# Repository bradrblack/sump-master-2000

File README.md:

<br clear="both"/>

# Sump Master 2000

An ESP32-C3 sump pump monitor. It detects the pump running from its vibration,
measures the water level and the air temperature/humidity, sends everything to
InfluxDB (via Telegraf on the LAN) for a Grafana timeline, and pushes pump
events, alarms and a daily report to your phone with [ntfy.sh](https://ntfy.sh).

There's no cloud service in the data path: readings go to a database on your own
network. [PLAN.md](PLAN.md) has the design and the remaining open questions.

The sketch is `src/sm2k.ino`, with small drivers for the level sensor
(`src/jsn_sr04t.*`) and the AHT20 (`src/aht20.*`).

## What it does

- **Pump on/off:** a GY-346 (ADXL346) accelerometer clamped to the pump or the
  discharge pipe. Samples at 400 Hz, high-passes each axis (~13 Hz cutoff) to
  reject gravity, footsteps and house rumble, and computes RMS over 250 ms
  windows. `RUN_CONFIRM_MS` of continuous vibration above `ON_RMS_THRESHOLD`
  starts a run; `STOP_CONFIRM_MS` of quiet below `OFF_RMS_THRESHOLD` ends it
  (3 s each).
- **Water level:** a JSN-SR04T waterproof ultrasonic sensor under the pit lid.
  Every 5 s it takes the median of a burst of 5 pings (one per 250 ms window, so
  vibration sampling never waits), corrected for the speed of sound at the
  measured air temperature. Level is reported as water depth above the pit
  floor.
- **Temperature/humidity:** an AHT20 on the same I2C bus, read every 10 s and
  CRC-checked.
- **Data to InfluxDB:** pump start/stop as it happens, and every 10 minutes the
  level, temperature, humidity and pump activity. See [Data](#data).
- **Home Assistant (optional):** state over MQTT, found automatically through
  MQTT Discovery. See [Home Assistant](#home-assistant).
- **ntfy pushes:** see [Notifications](#notifications).
- **A web page on the board** (`http://sm2k.local/`): live readings, the recent
  log, and the calibration settings, changeable from a phone. See
  [Web page](#web-page).
- **OTA updates** pushed from your computer over Wi-Fi, with automatic rollback if the
  new firmware isn't healthy. See [Updating](#updating-firmware).

The onboard NeoPixel (GPIO 8, dimmed) shows the state: **green** = all clear,
**blue** = pump running, **flashing red** = high water with the pump not running,
**flashing purple** = high water with the pump running.

Serial output (115200) prints a status line once a second:
`rms=0.208 max=0.219 loud=0 state=idle level=12.3cm air=17.9C/71% wifi=up tgq=0`
(`rms` is the latest 250 ms window, `max` the loudest of that second, `loud`
how many of its windows reached the stop threshold, `tgq` the number of points
waiting to be sent to Telegraf).

## Hardware and wiring

| Part | Connection |
|------|------------|
| GY-346 (ADXL346) SDA / SCL | GPIO 5 / GPIO 6 |
| AHT20 SDA / SCL | GPIO 5 / GPIO 6 (same bus) |
| JSN-SR04T Trig | GPIO 3 |
| JSN-SR04T Echo | GPIO 4, **straight to the pin** (3.3 V board, no divider) |
| JSN-SR04T VCC / GND | SuperMini 3V3 / GND |
| Status LED | GPIO 8 (onboard NeoPixel) |
| Sensor supply capacitors | 470 µF across 3V3/GND at each I2C sensor |

GPIO 2, 8 and 9 are boot strapping pins on the C3, so nothing else uses them.

**I2C reliability:** the bus runs at **100 kHz**. At 400 kHz, with long jumper
wires and no capacitors, the sensors dropped out and the board sometimes crashed
inside the I2C driver on a cold power-up. Short direct wires plus a 470 µF
capacitor across 3V3/GND at each sensor fixed it (14 hours overnight and 5 of 5
cold power-ups clean). Keep the capacitors.

**GY-346 note:** the ADXL346 is register-compatible with the ADXL345 and uses
the same Adafruit library, but reports device ID `0xE6` rather than `0xE5`, which
the library's `begin()` rejects. The firmware accepts either chip and enables
measurement itself. Its CS and SDO pins can stay unconnected (the module has
pull resistors). The AHT20+BMP280 board's BMP280 (0x77) is unused.

**Level sensor power:** use a **newer JSN-SR04T / AJ-SR04M board that runs from
3.3 V**; its Echo is then 3.3 V and needs no divider. An older 5 V board needs
one: Echo → 1 kΩ → GPIO 4 and GPIO 4 → 2 kΩ → GND. Measure Echo before
connecting it. The firmware enables a weak pull-down on GPIO 4 so a
disconnected Echo can't fire the interrupt from radio noise.
[PLAN.md](PLAN.md#jsn-sr04t-wiring) has the details.

**PCB and case:** the carrier PCB and 3D-printed case are in [hw/](hw/).

**Mounting the level sensor:** the JSN-SR04T is blind closer than about 20-25 cm
and can then report a double echo (about twice the real distance), which would
read as "low" just as the pit overflows. Mount the transducer **at least 30 cm
above the highest level the water can reach** (the pit rim), on a bracket or
riser. Readings closer than 25 cm are treated as "at or above the limit", never
as a real distance.

## Setup

1. **Secrets:**
   ```
   cp src/secrets.h.example src/secrets.h
   cp secrets.ini.example secrets.ini
   ```
   `src/secrets.h` holds Wi-Fi, the Telegraf URL and the ntfy topic;
   `secrets.ini` holds the OTA password (letters and digits), used both to build
   the firmware and to authenticate uploads. Both are git-ignored.
2. **Pit settings** in `platformio.ini` (`[env:sump]`): `SENSOR_TO_FLOOR_CM`,
   `HIGH_WATER_CM`, `HIGH_WATER_HYST_CM`, `MIN_DROP_CM`. The values there are
   placeholders until the sensor is mounted; see [Calibration](#calibration).
3. **InfluxDB, Telegraf and Grafana:** the board needs somewhere to send its
   data. If you don't already run these, follow
   [Setting up InfluxDB, Telegraf and Grafana](#setting-up-influxdb-telegraf-and-grafana)
   below, then put the Telegraf URL in `TELEGRAF_URL`. (Skip it, and leave
   `TELEGRAF_URL` out of `secrets.h`, if you only want the ntfy pushes.)
4. **ntfy:** subscribe to your `NTFY_TOPIC` in the ntfy app.
5. **First flash over USB** (it installs the OTA partition table):
   `pio run -t upload`.

## Updating firmware

After the first USB flash, update over Wi-Fi from your computer:

```
pio run -e sump-ota -t upload
```

- The board is found as `sm2k.local` (change `upload_port` in `platformio.ini` to
  an IP address if mDNS doesn't resolve).
- Updates are only accepted while the pump is idle (an upload pauses sampling
  for ~15 s). If the pump is running the upload fails with no response; run it
  again once the pump stops.
- **Rollback:** a new image runs as a trial. After 3 minutes with Wi-Fi up and
  every sensor that was working before the update working again, it's marked
  good and ntfy says `sump updated A -> B`. If it isn't healthy within 10
  minutes, crashes, or reboots during the trial (including failing to join
  Wi-Fi), the bootloader switches back to the previous firmware and ntfy says
  `update rolled back` with the reason.
- Bump `FIRMWARE_VERSION` in `src/sm2k.ino` for each release.
- Recovery if all else fails: USB flash (`pio run -t upload`).

## Setting up InfluxDB, Telegraf and Grafana

Skip this if you already run them. The data path is:

```
Sump Master  --HTTP POST-->  Telegraf (port 8186)  -->  InfluxDB  <--  Grafana
 (ESP32-C3)                  receives the board's        stores the     draws the
                             data and forwards it        time series    dashboard
```

- **InfluxDB 2.x** is the time-series database that stores the readings.
- **Telegraf** is a small collector. Here it just accepts the board's POSTs and
  writes them to InfluxDB (so the board never needs InfluxDB's token).
- **Grafana** draws the dashboard and sends the "silent" alert.

You need a computer that's always on, on the same network as the board: a
Raspberry Pi, a NAS, a spare PC or a home server. The easiest way to run all
three is Docker.

### 1. Start the three services (Docker)

Install [Docker](https://docs.docker.com/get-docker/), make an empty folder, and
create `docker-compose.yml` in it (change the passwords and token):

```yaml
services:
  influxdb:
    image: influxdb:2
    restart: unless-stopped
    ports: ["8086:8086"]
    volumes: ["influx-data:/var/lib/influxdb2"]
    environment:
      DOCKER_INFLUXDB_INIT_MODE: setup
      DOCKER_INFLUXDB_INIT_USERNAME: admin
      DOCKER_INFLUXDB_INIT_PASSWORD: change-this-password
      DOCKER_INFLUXDB_INIT_ORG: home
      DOCKER_INFLUXDB_INIT_BUCKET: sump
      DOCKER_INFLUXDB_INIT_ADMIN_TOKEN: change-this-admin-token

  telegraf:
    image: telegraf
    restart: unless-stopped
    ports: ["8186:8186"]
    depends_on: [influxdb]
    volumes: ["./sump.conf:/etc/telegraf/telegraf.conf:ro"]
    environment:
      INFLUX_URL: http://influxdb:8086
      INFLUX_ORG: home
      INFLUX_BUCKET: sump
      INFLUX_TOKEN: change-this-admin-token   # replace with a write-only token (step 2)

  grafana:
    image: grafana/grafana-oss
    restart: unless-stopped
    ports: ["3000:3000"]
    depends_on: [influxdb]
    volumes: ["grafana-data:/var/lib/grafana"]

volumes:
  influx-data:
  grafana-data:
```

Copy this project's `telegraf/sump.conf` into the same folder, then run
`docker compose up -d`. InfluxDB is now at `http://<server>:8086` (log in as
`admin`), Grafana at `http://<server>:3000` (first login `admin` / `admin`, it
asks you to change it).

Not using Docker? Install the three packages for your OS from their websites
(InfluxDB 2.x, Telegraf, Grafana), create an organisation and a bucket in
InfluxDB's setup page, copy `telegraf/sump.conf` to
`/etc/telegraf/telegraf.d/`, and put the variables from
`telegraf/sump.env.example` in Telegraf's environment file
(`/etc/default/telegraf` on Linux), then restart Telegraf.

### 2. Make two tokens in InfluxDB

In the InfluxDB web page (port 8086): **Load Data > API Tokens > Generate API
Token > Custom API Token**.

1. A token with **Write** access to the `sump` bucket only. Put it in Telegraf's
   `INFLUX_TOKEN` (replacing the admin token in the compose file) and run
   `docker compose up -d` again.
2. A token with **Read** access to the `sump` bucket, for Grafana (step 4).

### 3. Check Telegraf is listening

From any computer on the network (replace `<server>`):

```
curl -i -X POST http://<server>:8186/sump --data-binary 'sump_test,device=curl value=1'
```

`HTTP/1.1 204 No Content` means it worked. (If you get a connection error,
check the server's firewall allows port 8186.) Then set the URL in
`src/secrets.h`:

```
#define TELEGRAF_URL "http://<server>:8186/sump"
```

and flash the board. Within a minute you should see a `sump_boot` point: in
InfluxDB, **Data Explorer > sump bucket > `sump_boot`**, or in Grafana's Explore.
The 10-minute `sump` readings and pump events follow. If nothing appears, the
board's serial output says `[tg] ...` for each send and names the error (e.g.
"connection refused" means the address or port is wrong).

### 4. Add the dashboard to Grafana

1. In Grafana (port 3000): **Connections > Data sources > Add data source >
   InfluxDB**. Set **Query language** to **Flux**, **URL** to
   `http://influxdb:8086` (Docker) or `http://<server>:8086`, and under **InfluxDB
   Details** enter your organisation (`home`), the default bucket (`sump`) and
   the **read** token. Click **Save & test**.
2. **Dashboards > New > Import**, upload `grafana/sump-dashboard.json`, pick the
   data source you just made, and import.
3. Open the dashboard's settings > Variables and set `bucket` to `sump`, and
   `high_water_cm` / `min_drop_cm` to the same values as the firmware's
   `HIGH_WATER_CM` / `MIN_DROP_CM`.

To add the "silent" alert too, see [Grafana](#grafana) below; the data source
UID it asks for is the last part of the data source's page URL
(`.../connections/datasources/edit/<uid>`).

## Data

The board POSTs InfluxDB line protocol to Telegraf's `http_listener_v2`
(`TELEGRAF_URL`), timestamped with its own NTP-synced clock, so late or buffered
points land at the right time. All points are tagged `device=sump`.

| Measurement | When | Fields |
|---|---|---|
| `sump` | every 10 min, on the clock | `level_cm`, `distance_cm`, `level_status` (`ok`/`near_limit`/`missing`), `temp_c`, `humidity`, `running`, `pump_sensor` (1 = accelerometer answering), `cycles` and `run_s` (for the 10 minutes), `rssi`, `heap`; vibration for the 10 minutes: `rms_idle_avg`, `rms_idle_max`, `rms_run_avg`, `rms_run_min` (each only when there were such readings), and the thresholds in force, `rms_on`, `rms_off` |
| `sump_event` | pump start/stop | `event`, `running`, `seconds` (stop), `rms_avg` and `rms_min` (stop: that run's vibration), `level_cm` (start); `note="restart"` on a post-reboot correction, `note="sensor_lost"` if the accelerometer dropped out mid-run |
| `sump_cycle` | after each run | `seconds`, `level_before_cm`, `level_after_cm`, `drop_cm`, `result` (`ok`/`no_drop`/`unverified`) |
| `sump_alarm` | high water on/off | `type`, `active`, `level_cm` |
| `sump_boot` | each boot | `version`, `reason` |
| `sump_config` | settings changed on the web page | `rms_on`, `rms_off`, `run_confirm_s`, `stop_confirm_s`, `floor_cm`, `high_water_cm`, `hyst_cm`, `min_drop_cm` |

If Telegraf can't be reached, points queue on the board (150 lines, about a day
of readings plus events) and are sent in order when it's back; if the queue
fills, the oldest are dropped. The queue is in RAM, so a reboot loses it.

## Grafana

**Dashboard** (`grafana/sump-dashboard.json`, InfluxDB 2.x with Flux): import it
(Dashboards > New > Import), pick your InfluxDB (Flux) data source, then set the
`bucket` variable. Keep the `high_water_cm` and `min_drop_cm` variables equal to
the firmware's `HIGH_WATER_CM` and `MIN_DROP_CM`. All panels share one time
axis:

- Current values: pump on/off, water depth, air temperature, humidity, pump
  cycles in the range, and time since the last data.
- Pump and high-water state timeline.
- Water depth, with the level before and after each pump run and a dashed
  high-water line.
- Run time per cycle and level drop per cycle (a slow rise in run time, or a
  shrinking drop, is an early warning).
- Pump cycles and run time per day (US Eastern days).
- Temperature and humidity.
- Tables of recent pump cycles and of alarms and reboots, plus high-water and
  reboot annotations on every graph.
- Board health: Wi-Fi RSSI and free heap.

The JSON is generated by `tools/make_dashboard.py`: edit that and re-run it
rather than editing the JSON by hand.

**"Sump monitor silent" alert** (`grafana/sump-alerting.yaml`): fires to ntfy
when no sump data has arrived for 30 minutes, which covers what the board can't
report itself (no power, no Wi-Fi, Telegraf down, a hang). It sends a
"resolved" push when data returns.

- **Provisioning:** fill in the three `CHANGE_ME` values (ntfy topic, data
  source UID, bucket), copy the file to Grafana's `provisioning/alerting/`
  directory and restart Grafana. The rule routes to its own contact point, so
  your notification policies are untouched.
- **Or in the UI:** create a Webhook contact point with the URL
  `https://ntfy.sh/<topic>?template=grafana&ta=warning` (ntfy's built-in
  Grafana template turns the webhook JSON into a normal push; don't put `{{ }}`
  placeholders in the URL, Grafana tries to evaluate them itself). Then
  create an alert rule on the Flux query in the YAML file, with the condition
  "A is below 1", evaluated every 5 minutes, "Alert state if no data" set to
  **Alerting**, and the contact point selected under notifications.

## Notifications

All pushes go to `NTFY_TOPIC` (leave it out of `secrets.h` to disable them; they
are then only logged). They're queued and retried if the internet is down.

| Push | Priority |
|---|---|
| `sump started` / `sump stopped` in real time; the stop includes the run time, e.g. `Stopped at 2026-09-24 09:12:30 EDT (ran 28.8 s)` | default |
| **High water**: as soon as the level passes `HIGH_WATER_CM` (or reaches the sensor's limit), then every 30 minutes until it falls `HIGH_WATER_HYST_CM` below, then one "all clear" | urgent |
| **Pump ran but the level didn't drop** by `MIN_DROP_CM`: before/after levels and run time (clogged discharge, stuck check valve, pump running dry). If there was no level reading around the run: "can't verify" | high |
| **Daily report** just before the 3 AM reboot: pump state, water level, temperature and humidity, cycles/run time/longest run/highest water since the last report, firmware version | low (silent) |
| Sensor not responding (accelerometer, level sensor, AHT20), and recovered | high |
| Telegraf unreachable for 30 minutes, and reachable again | default |
| Exception reboots with the reason, e.g. `sump rebooted: WiFi down watchdog (reboot #2)` | default |
| OTA updated / rolled back | default / high |

ntfy.sh has per-IP rate and daily message limits for anonymous use, shared with
anything else on your public IP. Every pump cycle is two pushes, so check the
limits against a heavy wet-season day.

## Reliability

The firmware recovers on its own where possible and never fails silently.

| Mechanism | Behavior |
|-----------|----------|
| **Bounded Wi-Fi connect at boot** | If Wi-Fi isn't up within 30 s, reboot and retry instead of hanging. |
| **Wi-Fi watchdog** | If Wi-Fi drops it resets the radio and retries every 30 s; if it stays down for 2 minutes, reboot. |
| **Telegraf outage** | Doesn't reboot (that can't fix the server): data queues and one push says so. |
| **Accelerometer optional** | Every 30 s the accelerometer's device ID is read (without this a dead sensor reads as zeros and looks like an idle pump). If it's missing at boot, or fails three checks in a row, the board **keeps running without it**: pump on/off detection pauses, while water level, alarms, reporting and OTA carry on. One push says so, it's retried every 30 s with I2C bus recovery (clocking SCL to release a bus a sensor is holding low), and a push says when it's back. A run in progress when it drops out is closed with `note="sensor_lost"` and no run time. |
| **Level and AHT20 watchdogs** | Push an alert when there's been no reliable echo for 2 minutes, or no AHT20 reading for 5 minutes, and again when they recover. |
| **Suspect level readings** | A jump of more than 15 cm between readings is held until the next reading confirms it. |
| **Task watchdog** | A 30 s hardware watchdog resets a hung main loop; the reset is reported on the next boot. |
| **Nightly reboot** | 3 AM local time (`REBOOT_HOUR`, US Eastern via `TZ_STRING`, DST-aware) to guard against slow heap fragmentation, after sending the daily report. Held off while the pump runs, high water is active, a push is waiting or an OTA trial is running. The "already rebooted today" day is stored in flash so it can't reboot-loop within the hour. |
| **Unexpected reset detection** | A crash, watchdog or brownout reset is detected on the next boot and pushed. Power cycles, the reset button, flashing and deliberate restarts are not. |
| **Stuck "running" correction** | If the board reboots mid-run and the pump is idle 15 s after boot, a `stop` (with `note="restart"`, no run length) is recorded and pushed so nothing implies it's still running. |

## Web page

Open `http://sm2k.local/` (or the board's IP address, printed at boot as
`[web] ready`) from a phone or computer on the same network. No laptop or USB
cable is needed once the board is installed.

- **Live readings**, refreshed every 2 seconds: pump state, vibration, water
  depth, air temperature and humidity, Wi-Fi signal, and a chart of the last
  few minutes of vibration against the two thresholds.
- **Calibration readings:** the idle vibration since the last restart (average
  and peak), the last pump run (average and lowest), and suggested thresholds.
- **Settings** (calibration, below) and **Connections** (Telegraf address, ntfy
  topic, MQTT broker and login, admin password), saved on the board. Saving
  asks for a user name and password: `admin` and the admin password, which is
  the OTA password from `secrets.ini` until you change it on the page. It uses
  HTTP digest authentication, so the admin password itself isn't sent over the
  network. Anything you type into the form (an MQTT password, a new admin
  password) does cross your network unencrypted, since the page is plain HTTP.
  The ntfy topic and saved passwords are never shown back.
- **Log:** the last 120 log lines (everything the serial output shows except
  the once-a-second status line).

Viewing needs no password; anyone on your network can see the readings and the
log. The page is not reachable from the internet unless you set up a VPN.

Plain-data endpoints, if you want to script against it: `GET /api/status`
(JSON) and `GET /api/log?since=N` (text; the first line is the line count to
pass back as `since`).

## Home Assistant

The board can publish to an MQTT broker, and Home Assistant picks it up through
MQTT Discovery as one device, "Sump Master 2000". InfluxDB/Grafana, ntfy and
MQTT are independent: use any or all.

1. In Home Assistant, install an MQTT broker (the Mosquitto add-on) and the
   MQTT integration. The add-on needs a login: use a Home Assistant user, or
   add one in the add-on's configuration.
2. On the board's web page, under **Connections**, enter the broker's address
   (host name or IP, no `mqtt://`), port (1883), and the user name and
   password. Save. The line above the form shows "Home Assistant (MQTT)
   connected", or why it isn't.
3. The device appears under Settings > Devices & services > MQTT.

| Entity | Notes |
|---|---|
| Pump (running), High water (problem) | sent at once when they change |
| Water depth, Air temperature, Humidity, Vibration | every 30 s; "unknown" while a sensor has no current reading |
| Last pump run (s), Pump cycles since restart | |
| Level sensor, Pump sensor (problem) | diagnostic |
| Wi-Fi signal, Uptime, Firmware | diagnostic |

Topics: `sm2k/<device>/state` (retained JSON), `sm2k/<device>/status`
(`online`/`offline`; the broker publishes `offline` if the board disappears, so
Home Assistant shows the entities as unavailable), and
`homeassistant/<type>/sm2k_<device>/<entity>/config` for discovery.

The Grafana "Sump monitor silent" alert only exists if you use InfluxDB. With
Home Assistant alone, make an automation on the device becoming unavailable.

## Calibration

Every calibration value can be changed on the [web page](#web-page) without
reflashing. The values in `platformio.ini` are the defaults a board starts with
(and returns to with **Reset to defaults**); saved values survive restarts and
firmware updates.

| Setting | Default (`platformio.ini`) |
|---|---|
| Pump start / stop threshold (m/s² RMS) | `ON_RMS_THRESHOLD` 0.50 / `OFF_RMS_THRESHOLD` 0.30 |
| Seconds of vibration / quiet to count as started / stopped | `RUN_CONFIRM_MS` / `STOP_CONFIRM_MS`, 3 s each |
| Sensor to pit floor (cm) | `SENSOR_TO_FLOOR_CM` |
| High-water alarm depth, and how far below it clears (cm) | `HIGH_WATER_CM`, `HIGH_WATER_HYST_CM` |
| A run should lower the water by (cm) | `MIN_DROP_CM` |

- **Vibration thresholds:** let the pump run once, then read the web page's
  calibration readings: both thresholds belong between the idle average and
  the last run's lowest value (the page suggests a pair). The Grafana panel
  "Vibration: idle and running, against the thresholds" shows the same over
  days: both dashed lines should stay above the idle readings and below
  "Running lowest". The board on a desk idles at about 0.2 m/s².
- **Pit:** set the sensor-to-floor distance to the measured distance from the
  sensor to the empty pit floor (the page shows the current sensor-to-water
  distance). Every pump run is logged (and stored in `sump_cycle`) as
  `Pump cycle: on at X cm, off at Y cm, dropped Z cm`, so after a few real
  cycles set the high-water depth a few cm above the normal "on" level and the
  expected drop well below the normal drop.
- A settings change is recorded in InfluxDB (`sump_config`) and marked on the
  dashboard.

## Notes and gotchas

- Wi-Fi TX power is set to 15 dBm (`WIFI_TX_POWER`). This was needed on older
  ESP32-C3 SuperMini boards, which joined Wi-Fi on only about 1 in 3 boots at
  full power; **the newer "v2" boards with an external antenna don't have that
  problem and don't need it**. 15 dBm is a safe default; only lower it (e.g.
  `WIFI_POWER_8_5dBm`) if your board is flaky joining Wi-Fi.
- Log lines are timestamped (wall-clock time once NTP syncs, uptime before
  that) and the boot banner prints `FIRMWARE_VERSION`.
- The platform is pinned (`55.03.37`) because the unpinned "stable" release's
  esptool crashed mid-upload; don't unpin it.
- The USB port name changes each time the board re-enumerates; close any
  serial monitor before flashing, and restart the monitor after the board
  reboots.

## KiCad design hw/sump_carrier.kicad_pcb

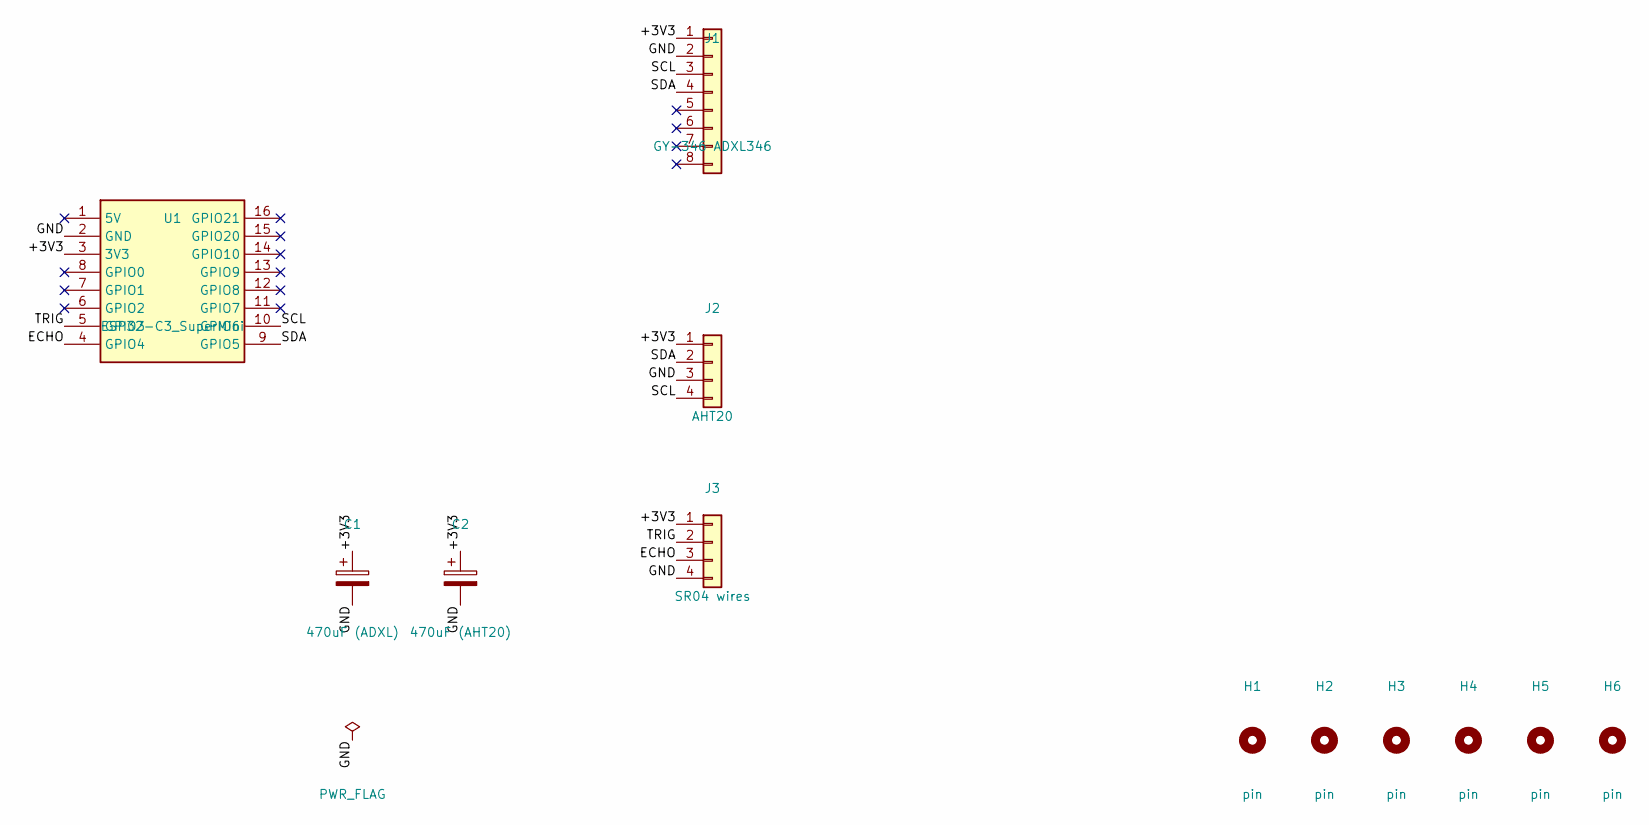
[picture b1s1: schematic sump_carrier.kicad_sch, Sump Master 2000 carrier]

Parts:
C1: 470uF (ADXL); CP_Radial_D7.5mm_P2.50mm
C2: 470uF (AHT20); CP_Radial_D7.5mm_P2.50mm
H1, H2, H3, H4, H5, H6: pin; CasePin_Hole_2.5mm
J1: GY-346 ADXL346; PinHeader_1x08_P2.54mm_Vertical
J2: AHT20; PinHeader_1x04_P2.54mm_Vertical
J3: SR04 wires; PinHeader_1x04_P2.54mm_Vertical
U1: ESP32-C3_SuperMini; ESP32-C3_SuperMini_FaceUp

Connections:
/+3V3: C1.1, C2.1, J1.1, J2.1, J3.1, U1.3 (3V3)
/ECHO: J3.3, U1.4 (GPIO4)
/GND: C1.2, C2.2, J1.2, J2.3, J3.4, U1.2 (GND)
/SCL: J1.3, J2.4, U1.10 (GPIO6)
/SDA: J1.4, J2.2, U1.9 (GPIO5)
/TRIG: J3.2, U1.5 (GPIO3)

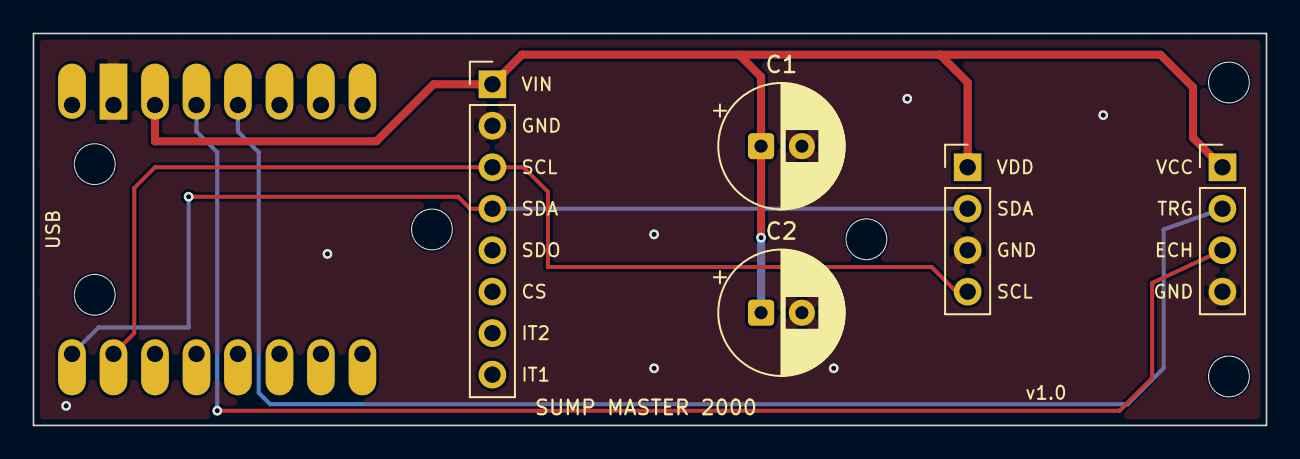
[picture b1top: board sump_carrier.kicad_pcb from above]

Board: 2 copper layers, 75.5 x 24.0 mm, 12 parts (0 on the bottom side), 6 nets.
